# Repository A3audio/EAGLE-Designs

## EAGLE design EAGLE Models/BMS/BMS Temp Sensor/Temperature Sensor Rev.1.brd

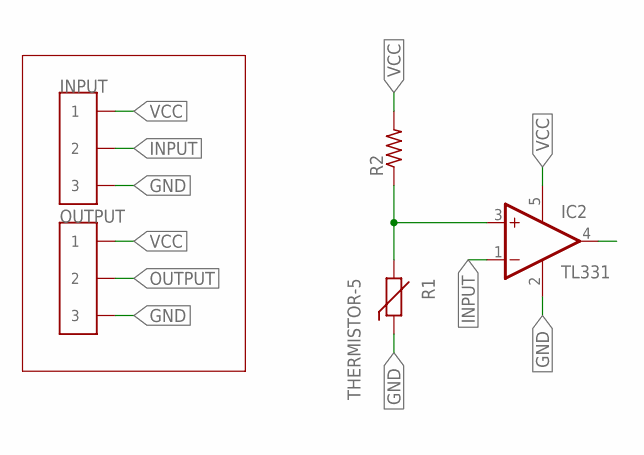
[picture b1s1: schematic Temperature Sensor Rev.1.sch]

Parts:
IC2: TL331; DBV-R-PDSO-G5
INPUT: CONN_3; CONNECTOR_3
OUTPUT: CONN_3; CONNECTOR_3
R1: THERMISTOR-5; R-5
R2: R-US_R0805; R0805

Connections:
GND: IC2.2 (GND), INPUT.5 (3), INPUT.6 (3), OUTPUT.5 (3), OUTPUT.6 (3), R1.1
INPUT: IC2.1 (-IN), INPUT.3 (2), INPUT.4 (2)
unnamed: IC2.3 (+IN), R1.2, R2.1
OUTPUT: IC2.4 (OUT), OUTPUT.3 (2), OUTPUT.4 (2)
VCC: IC2.5 (V+), INPUT.1, INPUT.2 (1), OUTPUT.1, OUTPUT.2 (1), R2.2

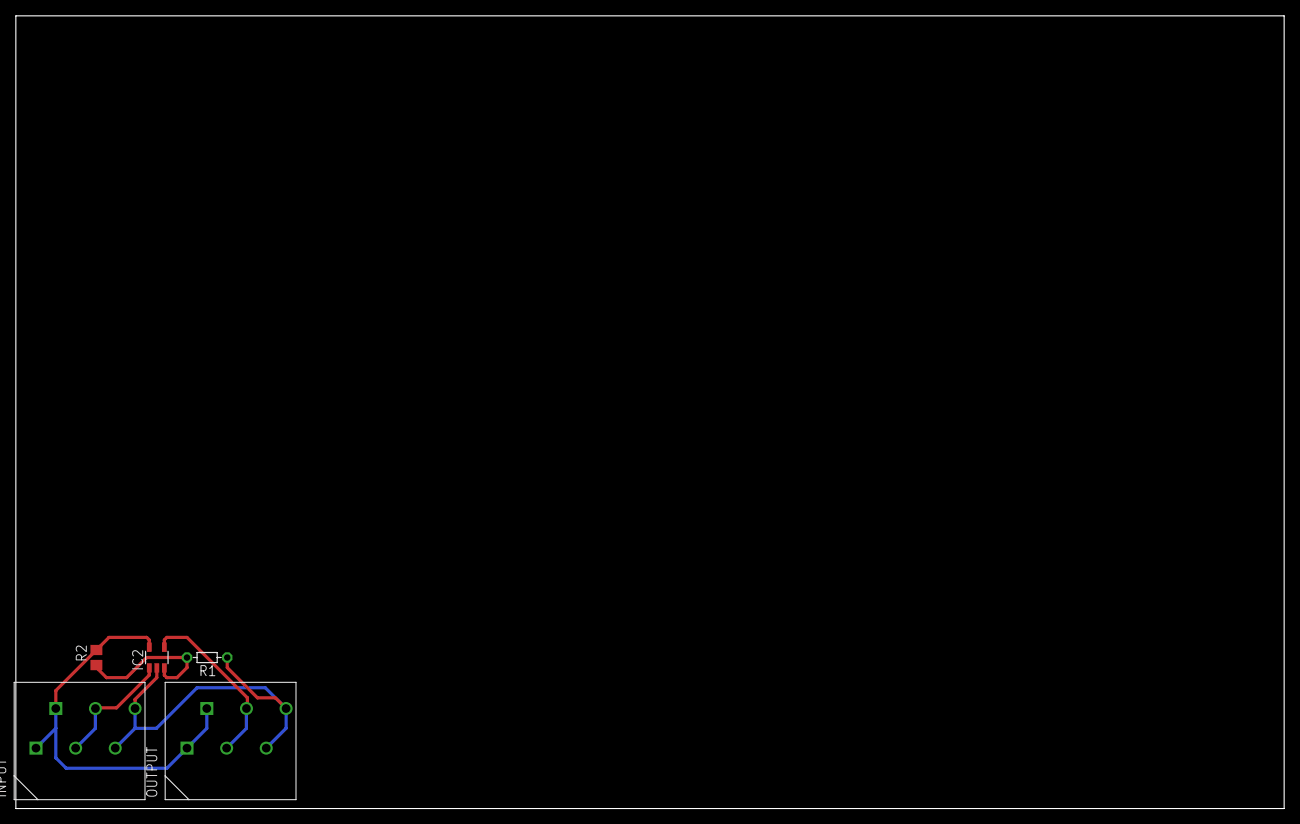
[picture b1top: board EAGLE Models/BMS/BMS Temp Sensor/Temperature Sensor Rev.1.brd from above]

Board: 2 copper layers, 160.0 x 100.0 mm, 5 parts (0 on the bottom side), 5 nets.

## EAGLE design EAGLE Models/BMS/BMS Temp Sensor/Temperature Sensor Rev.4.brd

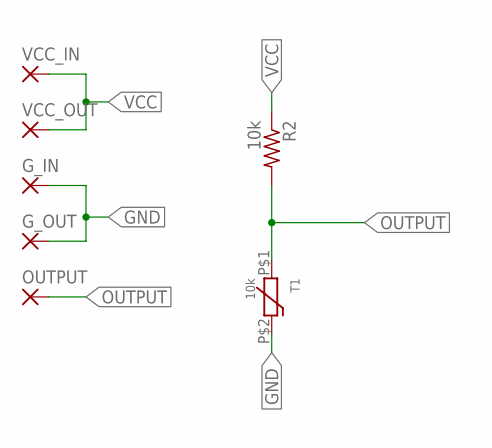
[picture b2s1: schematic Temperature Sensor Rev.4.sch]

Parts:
G_IN: 1,6/0,8
G_OUT: 1,6/0,8
OUTPUT: 1,6/0,8
R2: 10k; R0603
T1: 10k; 0603
VCC_IN: 1,6/0,8
VCC_OUT: 1,6/0,8

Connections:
GND: G_IN.1, G_OUT.1, T1.P$2
OUTPUT: OUTPUT.1, R2.2, T1.P$1
VCC: R2.1, VCC_IN.1, VCC_OUT.1

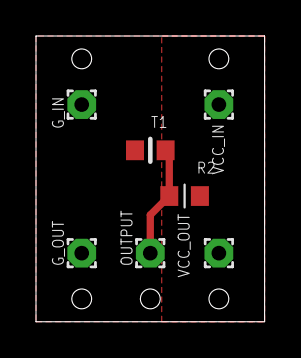
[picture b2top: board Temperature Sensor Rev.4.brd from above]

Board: 2 copper layers, 12.7 x 15.9 mm, 7 parts (0 on the bottom side), 3 nets.

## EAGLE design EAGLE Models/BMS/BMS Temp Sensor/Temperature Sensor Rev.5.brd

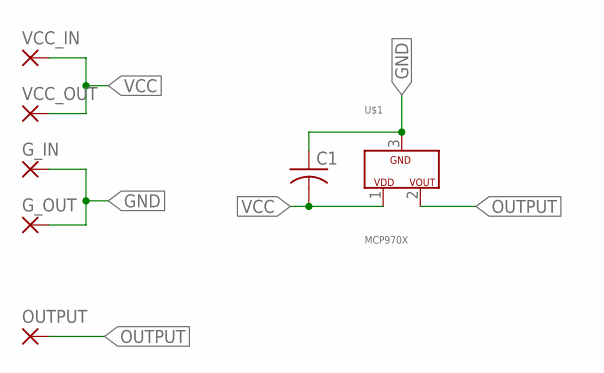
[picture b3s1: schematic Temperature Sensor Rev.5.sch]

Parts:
C1: C-USC0603; C0603
G_IN: 1,6/0,8
G_OUT: 1,6/0,8
OUTPUT: 1,6/0,8
U$1: MCP970X; SOT23
VCC_IN: 1,6/0,8
VCC_OUT: 1,6/0,8

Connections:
GND: C1.1, G_IN.1, G_OUT.1, U$1.3 (GND)
OUTPUT: OUTPUT.1, U$1.2 (VOUT)
VCC: C1.2, U$1.1 (VDD), VCC_IN.1, VCC_OUT.1

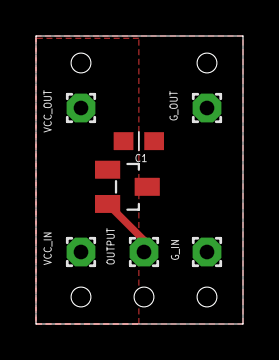
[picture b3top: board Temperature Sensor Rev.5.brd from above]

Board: 2 copper layers, 11.5 x 16.0 mm, 7 parts (0 on the bottom side), 3 nets.

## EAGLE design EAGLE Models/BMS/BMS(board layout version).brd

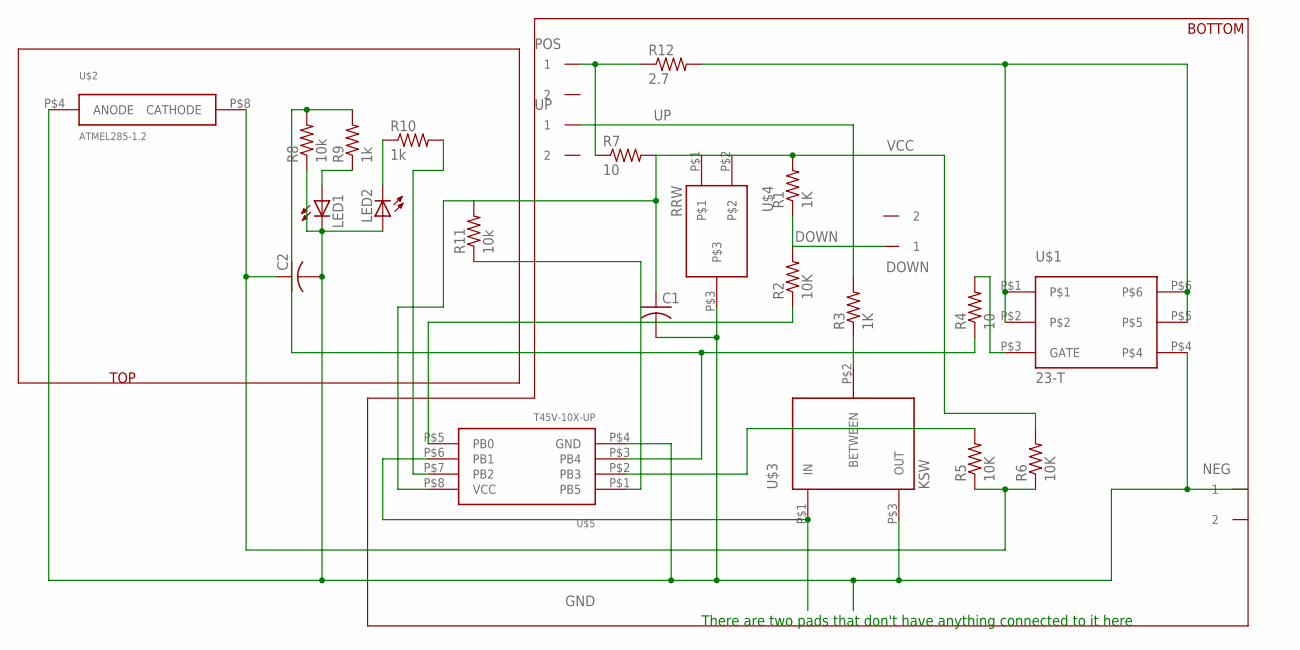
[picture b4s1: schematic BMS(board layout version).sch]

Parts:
C1, C2: C-USC0805; C0805
DOWN: CONN_1; CONNECTOR_1
LED1, LED2: LEDCHIPLED_1206; CHIPLED_1206
NEG: CONN_1; CONNECTOR_1
POS: CONN_1; CONNECTOR_1
R1, R3: 1K; R0805
R2, R5, R6: 10K; R0805
R4, R7: 10; R0805
R8, R11: 10k; R0805
R9, R10: 1k; R0805
R12: 2.7; R0805
U$1: 23-T; SOT-23-6
U$2: ATMEL285-1.2; 8-SOIC
U$3: KSW; SOT23-3
U$4: RRW; SOT23-3
U$5: T45V-10X-UP; TSOP-8
UP: CONN_1; CONNECTOR_1

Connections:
DOWN: DOWN.1, R1.1, R2.2
GND: C1.2, C2.2, LED1.C, LED2.A, NEG.1, R8.1, U$1.P$4, U$2.P$4 (ANODE), U$3.P$3 (OUT), U$4.P$3, U$5.P$4 (GND)
unnamed: R4.2, U$1.P$3 (GATE)
unnamed: R3.1, U$3.P$2 (BETWEEN)
unnamed: R2.1, U$5.P$5 (PB0)
unnamed: R5.2, U$5.P$2 (PB3)
unnamed: C2.1, R5.1, R6.1, U$2.P$8 (CATHODE)
unnamed: R12.2, U$1.P$1, U$1.P$2, U$1.P$5, U$1.P$6
unnamed: R4.1, R8.2, R9.2, U$5.P$3 (PB4)
unnamed: LED1.A, R9.1
unnamed: LED2.C, R10.1
unnamed: POS.1, R7.1, R12.1
unnamed: R10.2, U$5.P$7 (PB2)
unnamed: U$3.P$1 (IN), U$5.P$6 (PB1)
unnamed: R11.1, U$5.P$1 (PB5)
UP: R3.2, UP.1
VCC: C1.1, R1.2, R6.2, R7.2, R11.2, U$4.P$1, U$4.P$2, U$5.P$8 (VCC)

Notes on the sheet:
There are two pads that don't have anything connected to it here
TOP
BOTTOM

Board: 2 copper layers, 25 parts (0 on the bottom side), 17 nets, no tracks yet.

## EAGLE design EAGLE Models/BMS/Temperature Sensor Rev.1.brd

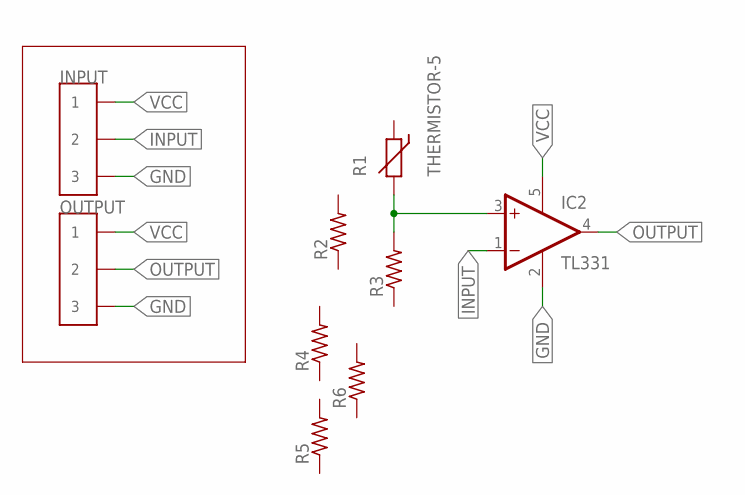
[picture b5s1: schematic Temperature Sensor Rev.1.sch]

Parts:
IC2: TL331; DBV-R-PDSO-G5
INPUT: CONN_3; CONNECTOR_3
OUTPUT: CONN_3; CONNECTOR_3
R1: THERMISTOR-5; R-5
R2, R3, R4, R5, R6: R-US_R0805; R0805

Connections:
GND: IC2.2 (GND), INPUT.5 (3), INPUT.6 (3), OUTPUT.5 (3), OUTPUT.6 (3)
INPUT: IC2.1 (-IN), INPUT.3 (2), INPUT.4 (2)
unnamed: IC2.3 (+IN), R1.2, R3.2
OUTPUT: IC2.4 (OUT), OUTPUT.3 (2), OUTPUT.4 (2)
VCC: IC2.5 (V+), INPUT.1, INPUT.2 (1), OUTPUT.1, OUTPUT.2 (1)

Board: 2 copper layers, 9 parts (0 on the bottom side), 5 nets, no tracks yet.

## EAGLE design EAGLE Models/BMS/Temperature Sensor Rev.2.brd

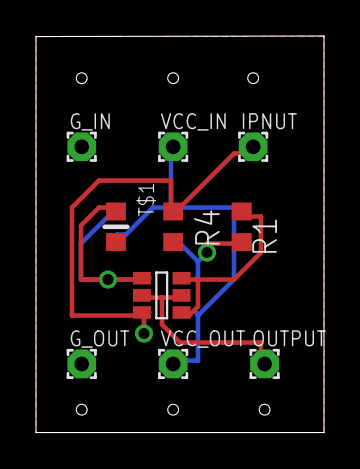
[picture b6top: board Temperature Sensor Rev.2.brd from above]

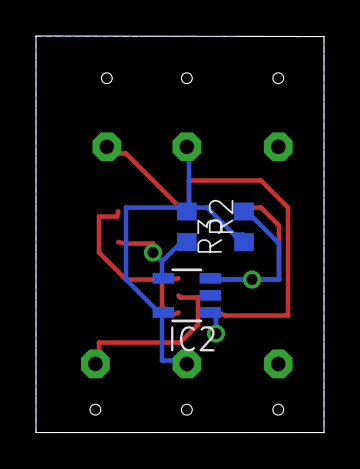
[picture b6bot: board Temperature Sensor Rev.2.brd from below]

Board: 2 copper layers, 16.0 x 22.0 mm, 13 parts (3 on the bottom side), 7 nets.

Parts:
G_IN: 1,6/0,8
G_OUT: 1,6/0,8
IC2: TL331; DBV-R-PDSO-G5
IPNUT: 1,6/0,8
OUTPUT: 1,6/0,8
R1, R2, R3, R4: R0603
T$1: THERMISTOR; 0603
VCC_IN: 1,6/0,8
VCC_OUT: 1,6/0,8
_: DMG6602; SOT23-6

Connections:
COMP_OUT: IC2.4, R1.2, R3.2
GND: G_IN.1, G_OUT.1, IC2.2, R4.2, T$1.P$2
INPUT: IC2.1, IPNUT.1, R4.1, _.P$6
MOS_IN: R1.1, _.P$1, _.P$3
OUTPUT: OUTPUT.1, _.P$2, _.P$5
THERM_OUT: IC2.3, R2.2, T$1.P$1, _.P$4
VCC: IC2.5, R2.1, R3.1, VCC_IN.1, VCC_OUT.1

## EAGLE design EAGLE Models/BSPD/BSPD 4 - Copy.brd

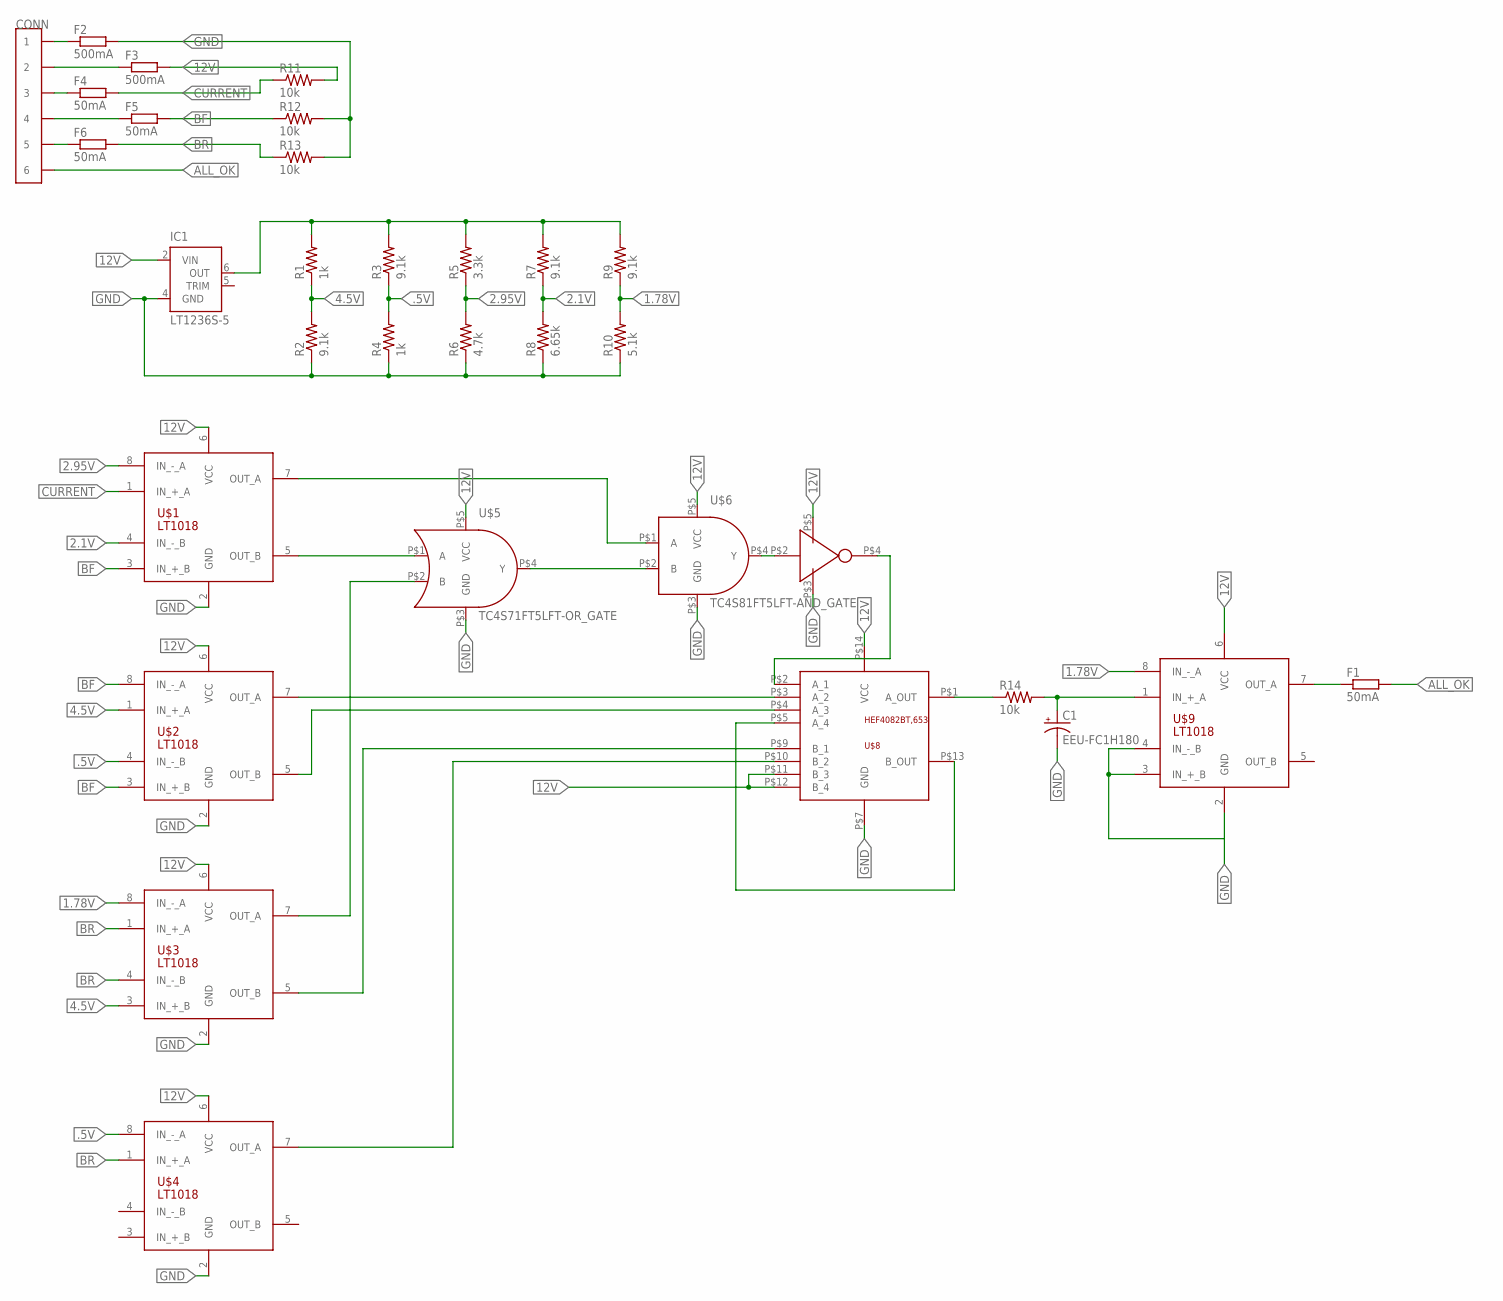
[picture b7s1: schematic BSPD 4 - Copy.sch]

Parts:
C1: EEU-FC1H180; E2-5
CONN: CONN_6; CONNECTOR_6
F1, F4, F5, F6: 50mA; R0603
F2, F3: 500mA; R0603
IC1: LT1236S-5; SOIC8
R1, R4: 1k; 0603-RES
R2, R3, R7, R9: 9.1k; 0603-RES
R5: 3.3k; 0603-RES
R6: 4.7k; 0603-RES
R8: 6.65k; 0603-RES
R10: 5.1k; 0603-RES
R11, R12, R13: 10k; 0603-RES
R14: 10k; R0603
U$1, U$2, U$3, U$4, U$9: LT1018; SOIC8
U$5: TC4S71FT5LFT-OR_GATE; SSOP5-P-0.95
U$6: TC4S81FT5LFT-AND_GATE; SSOP5-P-0.95
U$7: TC4S69F(TE85L,F); SSOP5-P-0.95
U$8: HEF4082BT,653; NXP_14_SOIC

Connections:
1.78V: R9.1, R10.2, U$3.8 (IN_-_A), U$9.8 (IN_-_A)
2.1V: R7.1, R8.2, U$1.4 (IN_-_B)
2.95V: R5.1, R6.2, U$1.8 (IN_-_A)
4.5V: R1.1, R2.2, U$2.1 (IN_+_A), U$3.3 (IN_+_B)
12V: F3.2, IC1.2 (VIN), R11.2, U$1.6 (VCC), U$2.6 (VCC), U$3.6 (VCC), U$4.6 (VCC), U$5.P$5 (VCC), U$6.P$5 (VCC), U$7.P$5 (VCC), U$8.P$11 (B_3), U$8.P$12 (B_4), U$8.P$14 (VCC), U$9.6 (VCC)
.5V: R3.1, R4.2, U$2.4 (IN_-_B), U$4.8 (IN_-_A)
ALL_OK: CONN.11 (6), CONN.12 (6), F1.2
BF: F5.2, R12.1, U$1.3 (IN_+_B), U$2.3 (IN_+_B), U$2.8 (IN_-_A)
BR: F6.2, R13.1, U$3.1 (IN_+_A), U$3.4 (IN_-_B), U$4.1 (IN_+_A)
CURRENT: F4.2, R11.1, U$1.1 (IN_+_A)
GND: C1.-, F2.2, IC1.4 (GND), R2.1, R4.1, R6.1, R8.1, R10.1, R12.2, R13.2, U$1.2 (GND), U$2.2 (GND), U$3.2 (GND), U$4.2 (GND), U$5.P$3 (GND), U$6.P$3 (GND), U$7.P$3 (GND), U$8.P$7 (GND), U$9.2 (GND), U$9.3 (IN_+_B), U$9.4 (IN_-_B)
unnamed: IC1.6 (OUT), R1.2, R3.2, R5.2, R7.2, R9.2
unnamed: U$1.5 (OUT_B), U$5.P$1 (A)
unnamed: U$3.7 (OUT_A), U$5.P$2 (B)
unnamed: U$5.P$4 (Y), U$6.P$2 (B)
unnamed: U$1.7 (OUT_A), U$6.P$1 (A)
unnamed: U$6.P$4 (Y), U$7.P$2 (IN)
unnamed: U$7.P$4 (OUT), U$8.P$2 (A_1)
unnamed: U$2.7 (OUT_A), U$8.P$3 (A_2)
unnamed: U$2.5 (OUT_B), U$8.P$4 (A_3)
unnamed: U$8.P$5 (A_4), U$8.P$13 (B_OUT)
unnamed: U$3.5 (OUT_B), U$8.P$9 (B_1)
unnamed: U$4.7 (OUT_A), U$8.P$10 (B_2)
unnamed: R14.1, U$8.P$1 (A_OUT)
unnamed: C1.+, R14.2, U$9.1 (IN_+_A)
unnamed: F1.1, U$9.7 (OUT_A)
unnamed: CONN.1, CONN.2 (1), F2.1
unnamed: CONN.3 (2), CONN.4 (2), F3.1
unnamed: CONN.5 (3), CONN.6 (3), F4.1
unnamed: CONN.7 (4), CONN.8 (4), F5.1
unnamed: CONN.9 (5), CONN.10 (5), F6.1

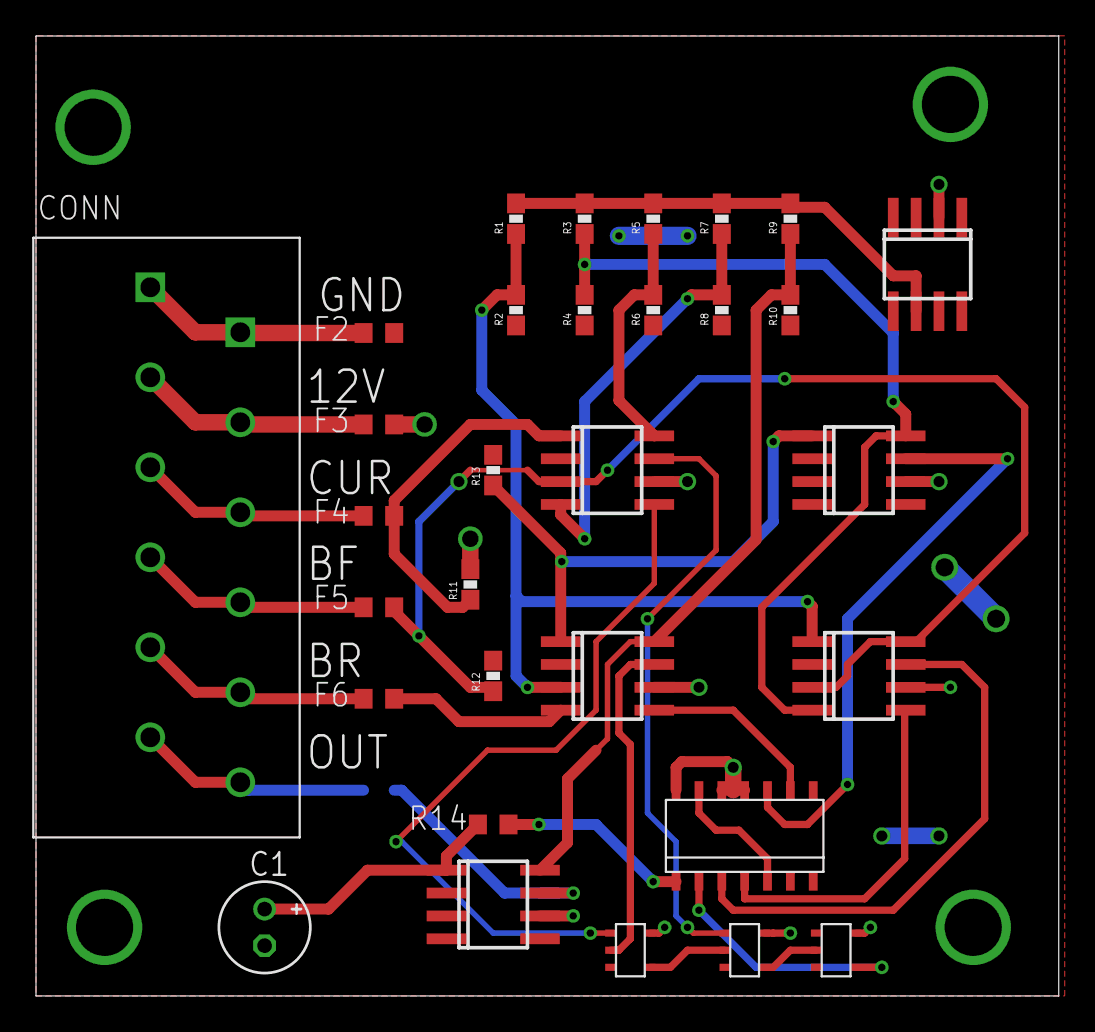
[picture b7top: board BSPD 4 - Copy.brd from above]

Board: 2 copper layers, 56.8 x 53.3 mm, 32 parts (1 on the bottom side), 31 nets.

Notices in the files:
parts and their libraries:
SparkFun-Resistors: Licensing: CC v3.0 Share-Alike You are welcome to use this library for commercial purposes.
